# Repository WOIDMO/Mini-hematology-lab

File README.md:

# Mini-hematology-lab
Open Source Mini Hematology Lab

The use of flow cytometry for common blood analysis in developing countries and field laboratories is problematic due to the high cost of the equipment, limited access to servicing and unreliable power. As an alternative to this technique we are developping a deep-learning AI powered microscope for analysis of blood and other samples.

Manual microscopy has served as a bedrock for many modern diagnostics, including diagnosing diseases such as Malaria. Direct visual identification of blood cells remains the gold standard for numerous diseases. However, this comes at the cost of tedious labor and human errors. Human fatigue has been identified as a crucial factor in reduced efficiency in microscopy based diagnostics. The same technological advancements that will one day lead to self-driving cars is currently mature enough to take over this task.

Based on the openflexure robotic microscope, we are developing a low-cost 3D printable autonomous platform capable of counting blood cell types and detecting parasite infections through the application of machine-learning. The device allows screening of more than 1.5 million red blood cells per minute for infections, which is 120 times faster compared to traditional manual microscopy. The cost of constructing the mini hematology lab is expected to be below 350 USD.

**Features:**

* Red blood cell count (RBC)
* White blood cell count (WBC)
* Differential white blood cell count
* Platelet count
* Parasite detection (eg Malaria)
* Battery powered (USB)
* Low cost

**Documentation:**

Please refer to the [wiki](https://github.com/WOIDMO/Mini-hematology-lab/wiki) 

**Progress:**

* 2021-09-01 Microscope design modifications: done
* 2021-10-01 Motor controller board design: done
* 2021-10-04 Blood staining protocol and started wiki: done
* 2021-xx-xx Software for AI hematology: pending
* 2021-xx-xx Software for AI malaria: pending
* 2021-xx-xx Documentation: pending

**Credits:**

The microscope is based on the [OpenFlexure](https://openflexure.org/) project started by Richard Bowman and maintained by the Bath Open INstrumentation Group.

The microscope is being extended for field and automated diagnostic use by the [WoIdMo](https://woidmo.org).

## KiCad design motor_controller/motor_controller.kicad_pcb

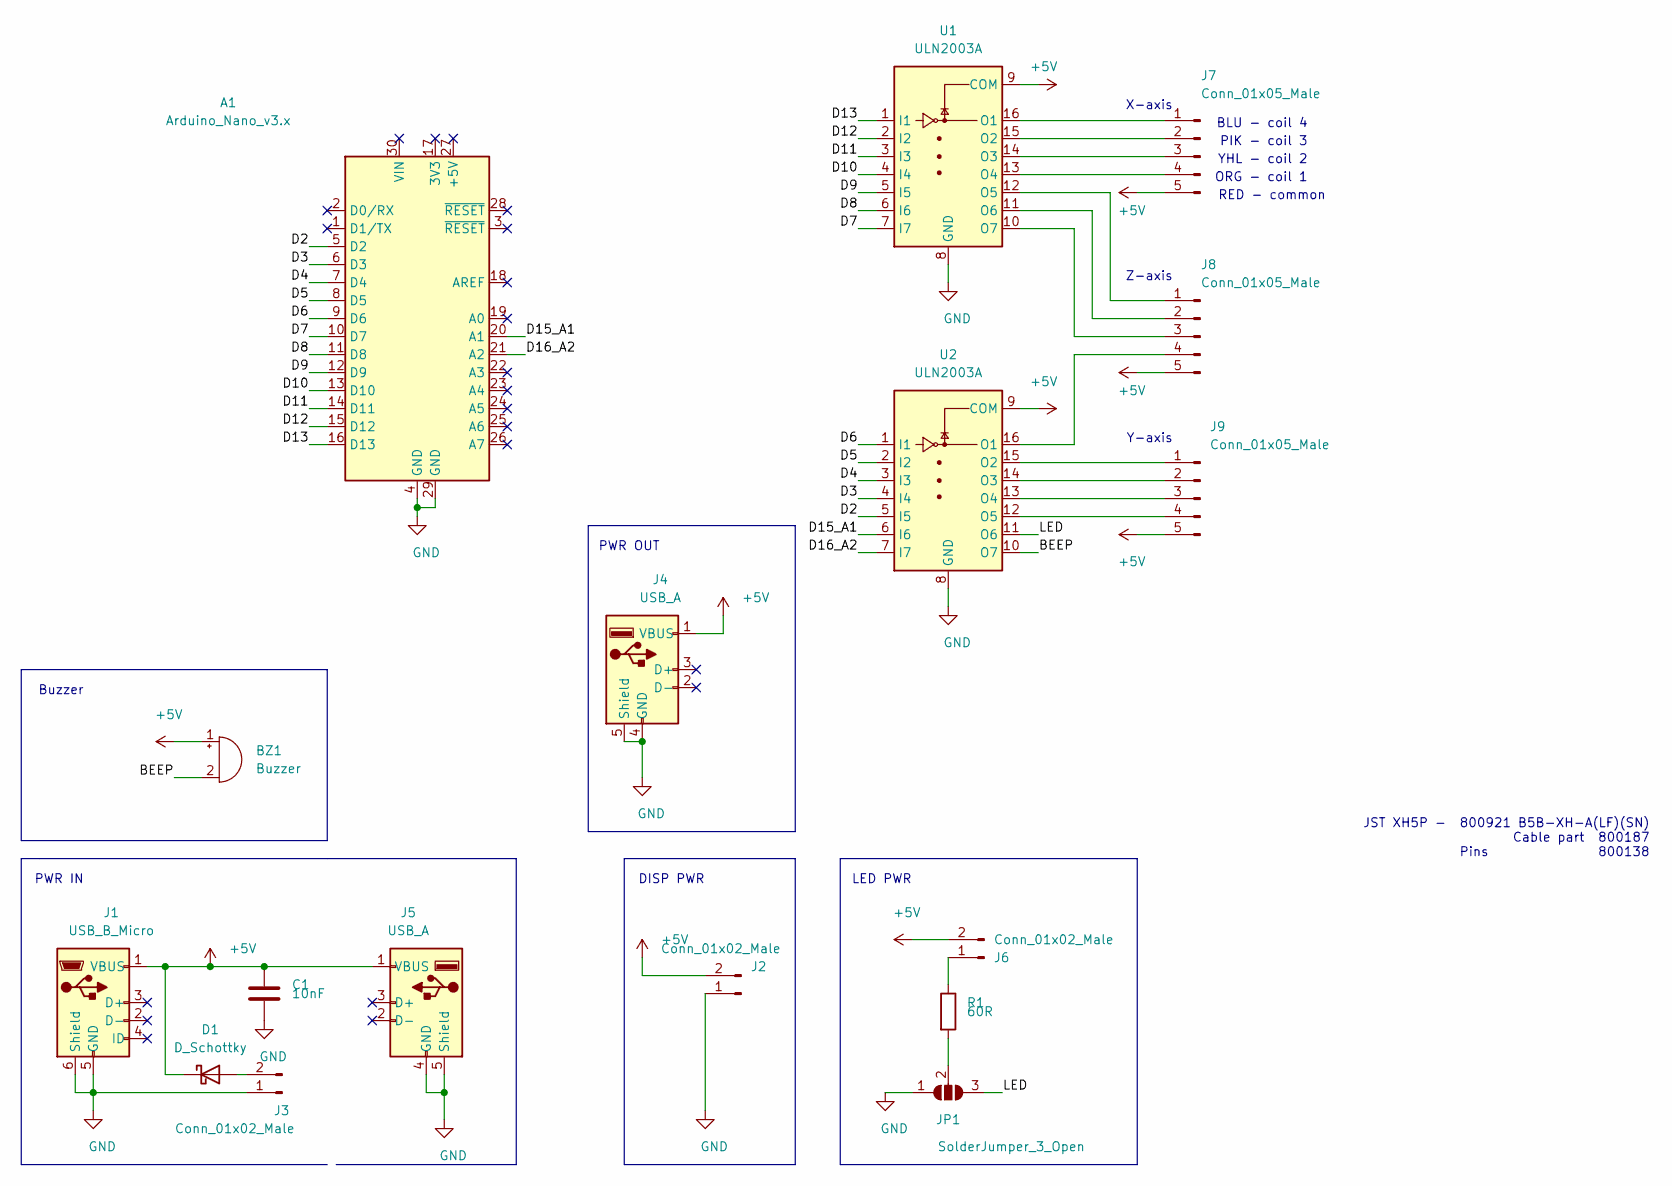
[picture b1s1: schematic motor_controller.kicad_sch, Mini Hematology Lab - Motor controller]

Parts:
A1: Arduino_Nano_v3.x; Arduino_Nano
BZ1: Buzzer; Buzzer_12x9.5RM7.6
C1: 10nF; C_0805_2012Metric_Pad1.15x1.40mm_HandSolder
D1: D_Schottky; D_SOD-123
J1: USB_B_Micro; USB_Micro-AB_Molex_47590-0001
J2, J3, J6: Conn_01x02_Male; JST_XH_B2B-XH-A_1x02_P2.50mm_Vertical
J4, J5: USB_A; USB_A_Molex_67643_Horizontal
J7, J8, J9: Conn_01x05_Male; JST_XH_B5B-XH-A_1x05_P2.50mm_Vertical
JP1: SolderJumper_3_Open; SolderJumper-3_P1.3mm_Open_Pad1.0x1.5mm
R1: 60R; R_0805_2012Metric_Pad1.15x1.40mm_HandSolder
U1, U2: ULN2003A; DIP-16_W7.62mm_Socket

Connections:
+5V: BZ1.1 (-), C1.1, D1.1 (K), J1.1 (VBUS), J2.2, J4.1 (VBUS), J5.1 (VBUS), J6.2, J7.5, J8.5, J9.5, U1.9 (COM), U2.9 (COM)
/BEEP: BZ1.2 (+), U2.10 (O7)
/D2: A1.5 (D2), U2.5 (I5)
/D3: A1.6 (D3), U2.4 (I4)
/D4: A1.7 (D4), U2.3 (I3)
/D5: A1.8 (D5), U2.2 (I2)
/D6: A1.9 (D6), U2.1 (I1)
/D7: A1.10 (D7), U1.7 (I7)
/D8: A1.11 (D8), U1.6 (I6)
/D9: A1.12 (D9), U1.5 (I5)
/D10: A1.13 (D10), U1.4 (I4)
/D11: A1.14 (D11), U1.3 (I3)
/D12: A1.15 (D12), U1.2 (I2)
/D13: A1.16 (D13), U1.1 (I1)
/D15_A1: A1.20 (A1), U2.6 (I6)
/D16_A2: A1.21 (A2), U2.7 (I7)
/LED: JP1.3 (B), U2.11 (O6)
GND: A1.4 (GND), A1.29 (GND), C1.2, J1.5 (GND), J1.6 (Shield), J2.1, J3.1, J4.4 (GND), J4.5 (Shield), J5.4 (GND), J5.5 (Shield), JP1.1 (A), U1.8 (GND), U2.8 (GND)
unnamed: D1.2 (A), J3.2
unnamed: J6.1, R1.1
unnamed: J7.1, U1.16 (O1)
unnamed: J7.2, U1.15 (O2)
unnamed: J7.3, U1.14 (O3)
unnamed: J7.4, U1.13 (O4)
unnamed: J8.1, U1.12 (O5)
unnamed: J8.2, U1.11 (O6)
unnamed: J8.3, U1.10 (O7)
unnamed: J8.4, U2.16 (O1)
unnamed: J9.1, U2.15 (O2)
unnamed: J9.2, U2.14 (O3)
unnamed: J9.3, U2.13 (O4)
unnamed: J9.4, U2.12 (O5)
unnamed: JP1.2 (C), R1.2

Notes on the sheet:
Buzzer
PWR IN
PWR OUT
DISP PWR
LED PWR
X-axis
Z-axis
Y-axis
BLU - coil 4
PIK - coil 3
YHL - coil 2
ORG - coil 1
RED - common
JST XH5P - 800921 B5B-XH-A(LF)(SN) Cable part 800187 Pins 800138

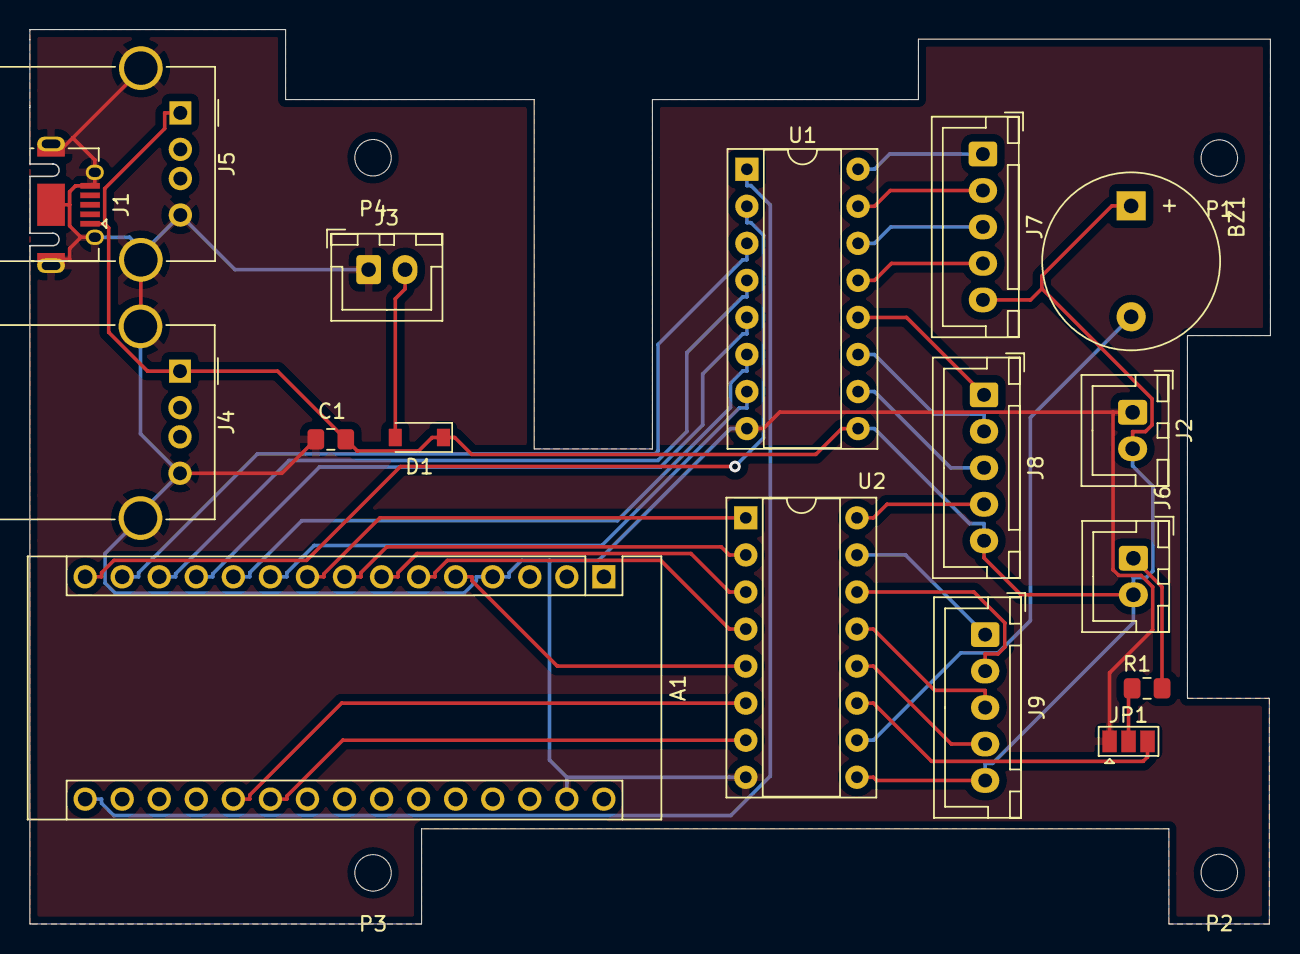
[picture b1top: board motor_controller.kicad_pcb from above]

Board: 2 copper layers, 85.0 x 61.3 mm, 21 parts (0 on the bottom side), 33 nets.

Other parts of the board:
P1, P2, P3, P4: MountingHole_2.5mm

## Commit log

2021-10-04 Create 1_Documentation_is_in_the_Wiki
